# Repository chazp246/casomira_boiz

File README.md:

# Moje repo na desky atd. 
Nějaký to základní verzovaní
+ používat nějaký ten time tracker na hodiny
+ tabulka s BOM a náklady https://docs.google.com/spreadsheets/d/1U5YpFSBs-wufp3I8VY69B08vQyyNULmpqPkYMU48hfg/edit?usp=sharing

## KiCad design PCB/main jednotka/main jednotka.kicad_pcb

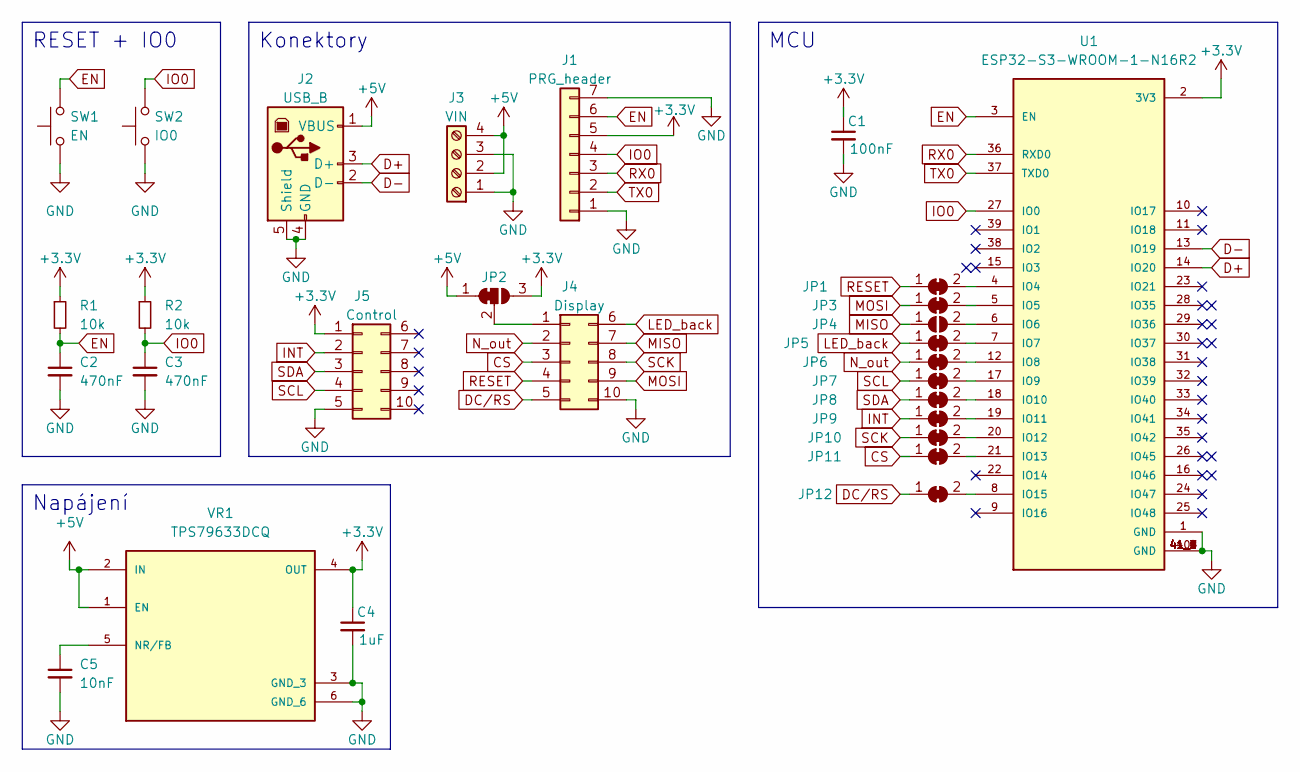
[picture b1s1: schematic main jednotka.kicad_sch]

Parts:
C1: 100nF; C_0805_2012Metric_Pad1.18x1.45mm_HandSolder
C2, C3: 470nF; C_0805_2012Metric
C4: 1uF; C_0805_2012Metric_Pad1.18x1.45mm_HandSolder
C5: 10nF; C_0805_2012Metric_Pad1.18x1.45mm_HandSolder
J1: PRG_header; PinHeader_1x07_P2.54mm_Vertical
J2: USB_B; PinHeader_1x04_P2.54mm_Vertical
J3: VIN; TerminalBlock_RND_205-00014_1x04_P5.00mm_Horizontal
J4: Display; PinSocket_2x05_P2.54mm_Vertical
J5: Control; PinSocket_2x05_P2.54mm_Vertical
JP1, JP3, JP5, JP6, JP7, JP8, JP9, JP10, JP11, JP12: SolderJumper_2_Bridged; SolderJumper-2_P1.3mm_Bridged_RoundedPad1.0x1.5mm
JP2: SolderJumper_3_Bridged12; SolderJumper-3_P1.3mm_Bridged12_RoundedPad1.0x1.5mm
JP4: jumper
R1, R2: 10k; R_0805_2012Metric
SW1: EN; SW_SPST_CK_RS282G05A3
SW2: IO0; SW_SPST_CK_RS282G05A3
U1: ESP32-S3-WROOM-1-N16R2; XCVR_ESP32-S3-WROOM-1-N16R2; PARTREV v1.0
VR1: TPS79633DCQ; VREG_TPS79633DCQ; PARTREV P

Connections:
+3.3V: C1.1, C4.1, J1.5, J5.1, JP2.3 (B), R1.1, R2.1, U1.2 (3V3), VR1.4 (OUT)
+5V: J2.1 (VBUS), J3.2, J3.4, JP2.1 (A), VR1.1 (EN), VR1.2 (IN)
CS: J4.3, JP11.1 (A)
D+: J2.3 (D+), U1.14 (IO20)
D-: J2.2 (D-), U1.13 (IO19)
DC/RS: J4.5, JP12.1 (A)
EN: C2.1, J1.6, R1.2, SW1.2, U1.3 (EN); also elsewhere on the board
GND: C1.2, C2.2, C3.2, C4.2, C5.2, J1.1, J1.7, J2.4 (GND), J2.5 (Shield), J3.1, J3.3, J4.10, J5.5, SW1.1, SW2.1, U1.1 (GND), U1.40 (GND), U1.41_1 (GND), U1.41_2 (GND), U1.41_3 (GND), U1.41_4 (GND), U1.41_5 (GND), U1.41_6 (GND), U1.41_7 (GND), U1.41_8 (GND), U1.41_9 (GND), U1.41_10, U1.41_11, U1.41_12, U1.41_13, U1.41_14, U1.41_15, U1.41_16, U1.41_17, U1.41_18, U1.41_19, U1.41_20, U1.41_21, VR1.3 (GND_3), VR1.6 (GND_6), VR1.7, VR1.8, VR1.9, VR1.10, VR1.11, VR1.12, VR1.13, VR1.14, VR1.15, VR1.16; also elsewhere on the board
INT: J5.2, JP9.1 (A)
IO0: C3.1, J1.4, R2.2, SW2.2, U1.27 (IO0); also elsewhere on the board
LED_back: J4.6, JP5.1 (A)
MISO: J4.7, JP4.1 (A)
MOSI: J4.9, JP3.1 (A)
N_out: J4.2, JP6.1 (A)
unnamed: C5.1, VR1.5 (NR/FB)
unnamed: J4.1, JP2.2 (C)
unnamed: JP1.2 (B), U1.4 (IO4)
unnamed: JP3.2 (B), U1.5 (IO5)
unnamed: JP4.2 (B), U1.6 (IO6)
unnamed: JP5.2 (B), U1.7 (IO7)
unnamed: JP12.2 (B), U1.8 (IO15)
unnamed: JP6.2 (B), U1.12 (IO8)
unnamed: JP7.2 (B), U1.17 (IO9)
unnamed: JP8.2 (B), U1.18 (IO10)
unnamed: JP9.2 (B), U1.19 (IO11)
unnamed: JP10.2 (B), U1.20 (IO12)
unnamed: JP11.2 (B), U1.21 (IO13)
RESET: J4.4, JP1.1 (A)
RX0: J1.3, U1.36 (RXD0)
SCK: J4.8, JP10.1 (A)
SCL: J5.4, JP7.1 (A)
SDA: J5.3, JP8.1 (A)
TX0: J1.2, U1.37 (TXD0)

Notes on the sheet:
Napájení
RESET + IO0
MCU
Konektory

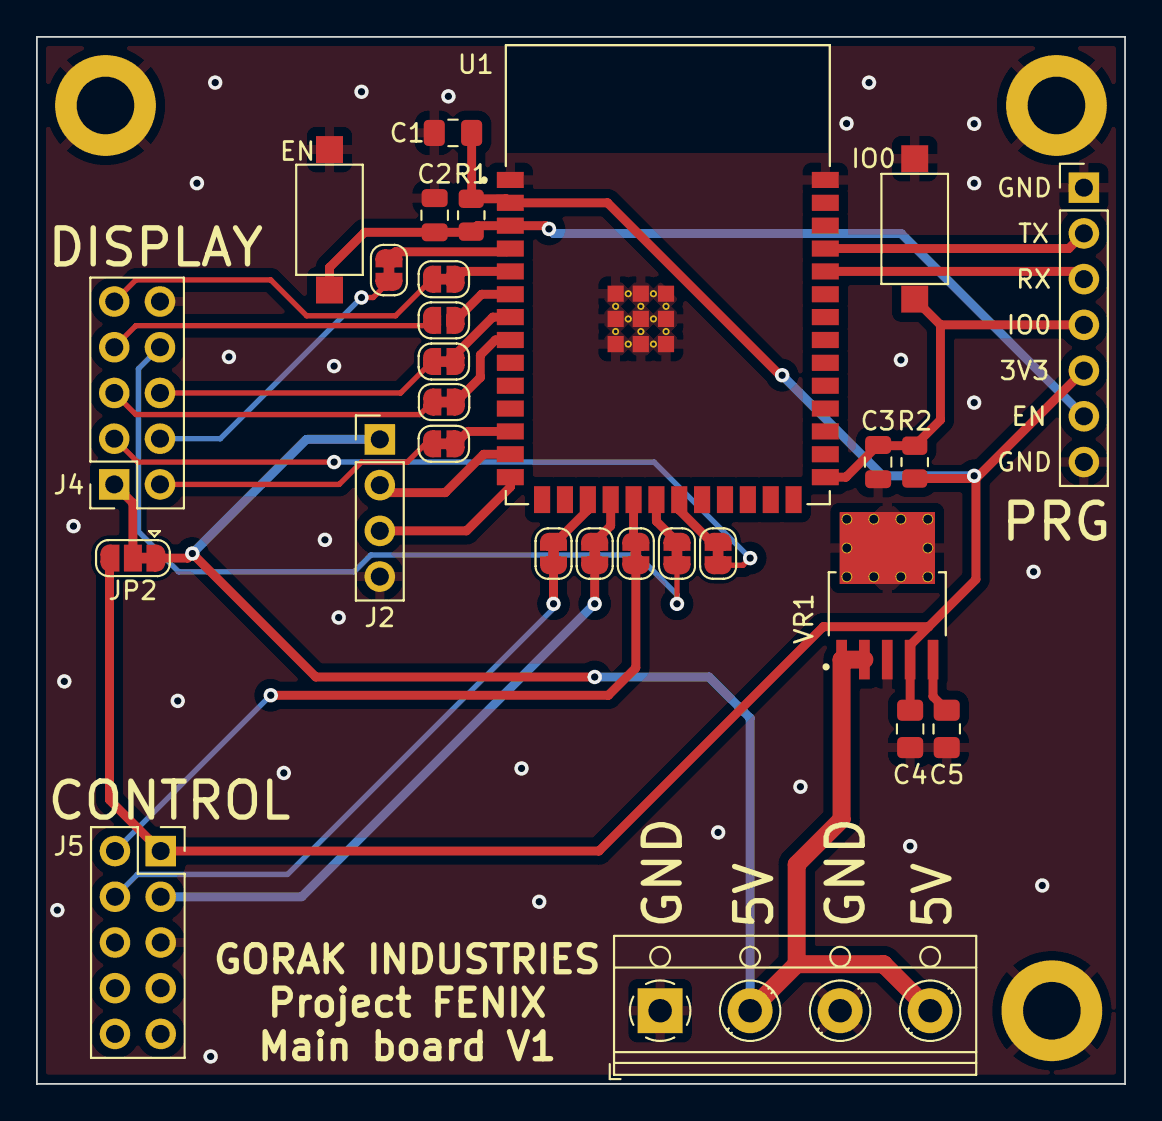
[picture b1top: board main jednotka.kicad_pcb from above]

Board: 2 copper layers, 60.5 x 58.2 mm, 28 parts (0 on the bottom side), 33 nets.

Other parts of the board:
EN: EN; SW_SPST_CK_RS282G05A3
IO0: IO0; SW_SPST_CK_RS282G05A3

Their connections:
EN: EN.2; also elsewhere on the board
GND: EN.1, IO0.1; also elsewhere on the board
IO0: IO0.2; also elsewhere on the board

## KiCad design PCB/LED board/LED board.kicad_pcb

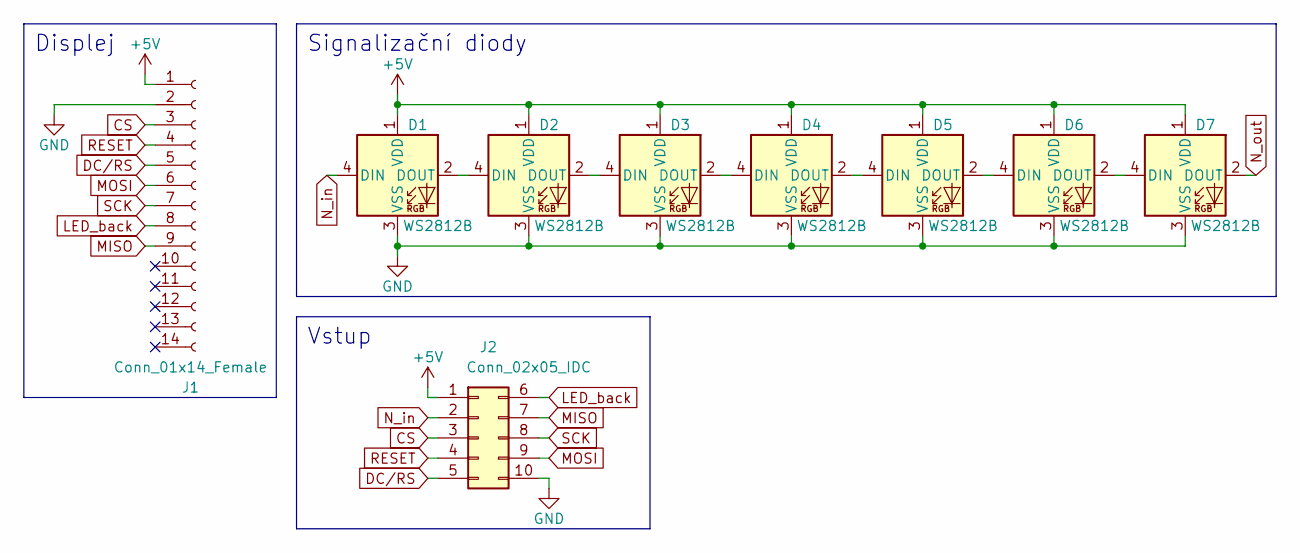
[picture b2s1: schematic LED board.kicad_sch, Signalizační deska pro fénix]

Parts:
D1, D2, D3, D4, D5, D6, D7: WS2812B; LED_WS2812B_PLCC4_5.0x5.0mm_P3.2mm
J1: Conn_01x14_Female; PinHeader_1x14_P2.54mm_Vertical
J2: Conn_02x05_IDC; PinSocket_2x05_P2.54mm_Horizontal

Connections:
+5V: D1.1 (VDD), D2.1 (VDD), D3.1 (VDD), D4.1 (VDD), D5.1 (VDD), D6.1 (VDD), D7.1 (VDD), J1.1, J2.1
CS: J1.3, J2.3
DC/RS: J1.5, J2.5
GND: D1.3 (VSS), D2.3 (VSS), D3.3 (VSS), D4.3 (VSS), D5.3 (VSS), D6.3 (VSS), D7.3 (VSS), J1.2, J2.10
LED_back: J1.8, J2.6
MISO: J1.9, J2.7
MOSI: J1.6, J2.9
N_in: D1.4 (DIN), J2.2
N_out: D7.2 (DOUT)
unnamed: D1.2 (DOUT), D2.4 (DIN)
unnamed: D2.2 (DOUT), D3.4 (DIN)
unnamed: D3.2 (DOUT), D4.4 (DIN)
unnamed: D4.2 (DOUT), D5.4 (DIN)
unnamed: D5.2 (DOUT), D6.4 (DIN)
unnamed: D6.2 (DOUT), D7.4 (DIN)
RESET: J1.4, J2.4
SCK: J1.7, J2.8

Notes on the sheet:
Vstup
Signalizační diody
Displej

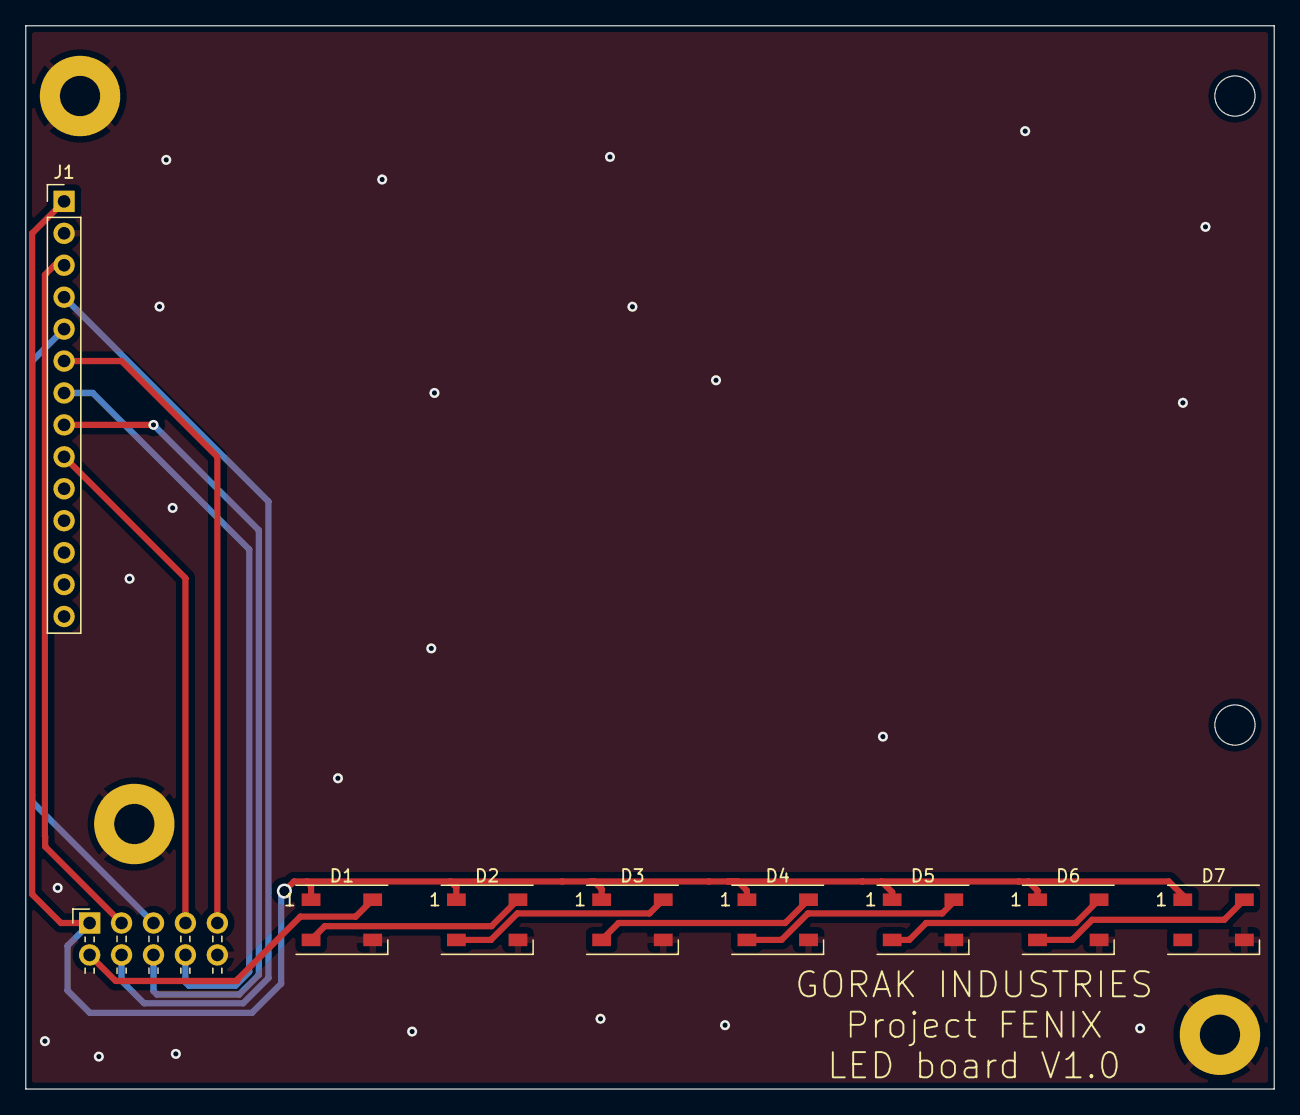
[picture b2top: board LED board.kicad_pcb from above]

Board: 2 copper layers, 99.3 x 84.6 mm, 9 parts (0 on the bottom side), 16 nets.

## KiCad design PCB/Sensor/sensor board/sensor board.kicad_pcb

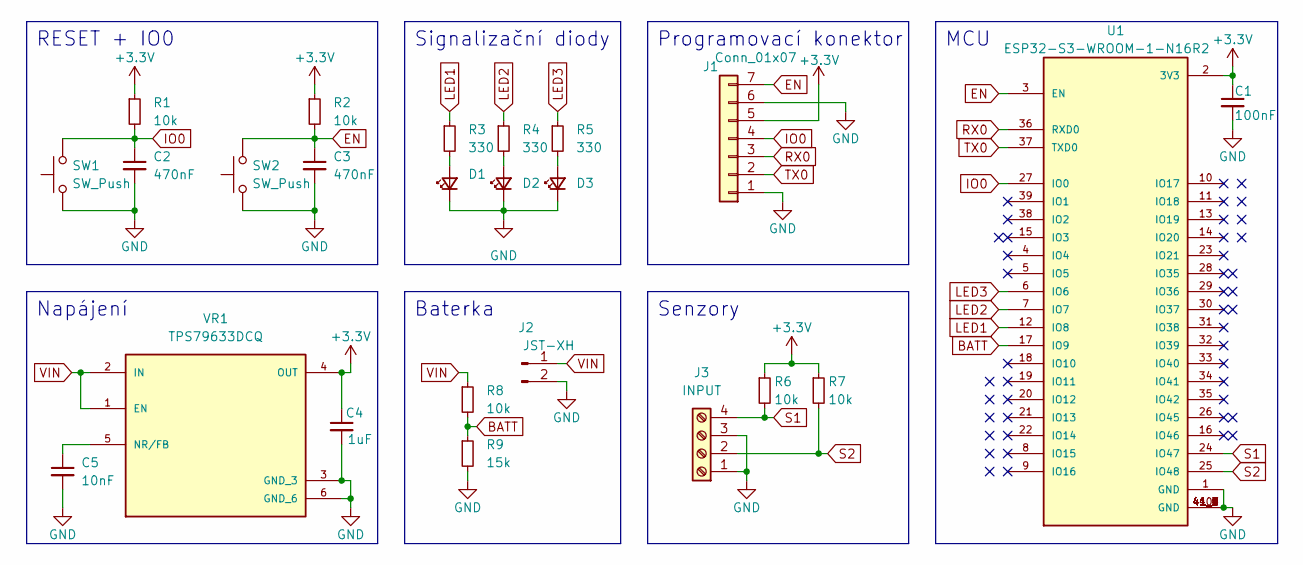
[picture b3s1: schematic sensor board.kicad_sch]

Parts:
C1: 100nF; C_0805_2012Metric_Pad1.18x1.45mm_HandSolder
C2, C3: 470nF; C_0805_2012Metric_Pad1.18x1.45mm_HandSolder
C4: 1uF; C_0805_2012Metric_Pad1.18x1.45mm_HandSolder
C5: 10nF; C_0805_2012Metric_Pad1.18x1.45mm_HandSolder
D1, D2, D3: LED_Small; LED_0805_2012Metric_Pad1.15x1.40mm_HandSolder
J1: Conn_01x07; PinHeader_1x07_P2.54mm_Vertical
J2: JST-XH; PinHeader_1x02_P2.54mm_Vertical
J3: INPUT; TerminalBlock_RND_205-00014_1x04_P5.00mm_Horizontal
R1, R2, R6, R7, R8: 10k; R_0805_2012Metric_Pad1.20x1.40mm_HandSolder
R3, R4, R5: 330; R_0805_2012Metric_Pad1.20x1.40mm_HandSolder
R9: 15k; R_0805_2012Metric_Pad1.20x1.40mm_HandSolder
SW1, SW2: SW_Push; SW_SPST_CK_RS282G05A3
U1: ESP32-S3-WROOM-1-N16R2; XCVR_ESP32-S3-WROOM-1-N16R2; PARTREV v1.0
VR1: TPS79633DCQ; VREG_TPS79633DCQ; PARTREV P

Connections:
+3.3V: C1.1, C4.1, J1.5, R1.1, R2.1, R6.1, R7.1, U1.2 (3V3), VR1.4 (OUT)
BATT: R8.2, R9.1, U1.17 (IO9)
EN: C3.1, J1.7, R2.2, SW2.2, U1.3 (EN)
GND: C1.2, C2.2, C3.2, C4.2, C5.2, D1.1 (K), D2.1 (K), D3.1 (K), J1.1, J1.6, J2.2, J3.1, J3.3, R9.2, SW1.1, SW2.1, U1.1 (GND), U1.40 (GND), U1.41_1 (GND), U1.41_2 (GND), U1.41_3 (GND), U1.41_4 (GND), U1.41_5 (GND), U1.41_6 (GND), U1.41_7 (GND), U1.41_8 (GND), U1.41_9 (GND), U1.41_10, U1.41_11, U1.41_12, U1.41_13, U1.41_14, U1.41_15, U1.41_16, U1.41_17, U1.41_18, U1.41_19, U1.41_20, U1.41_21, VR1.3 (GND_3), VR1.6 (GND_6), VR1.7, VR1.8, VR1.9, VR1.10, VR1.11, VR1.12, VR1.13, VR1.14, VR1.15, VR1.16
IO0: C2.1, J1.4, R1.2, SW1.2, U1.27 (IO0)
LED1: R3.1, U1.12 (IO8)
LED2: R4.1, U1.7 (IO7)
LED3: R5.1, U1.6 (IO6)
unnamed: C5.1, VR1.5 (NR/FB)
unnamed: D1.2 (A), R3.2
unnamed: D2.2 (A), R4.2
unnamed: D3.2 (A), R5.2
RX0: J1.3, U1.36 (RXD0)
S1: J3.4, R6.2, U1.24 (IO47)
S2: J3.2, R7.2, U1.25 (IO48)
TX0: J1.2, U1.37 (TXD0)
VIN: J2.1, R8.1, VR1.1 (EN), VR1.2 (IN)

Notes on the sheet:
Napájení
RESET + IO0
Programovací konektor
Baterka
MCU
Signalizační diody
Senzory

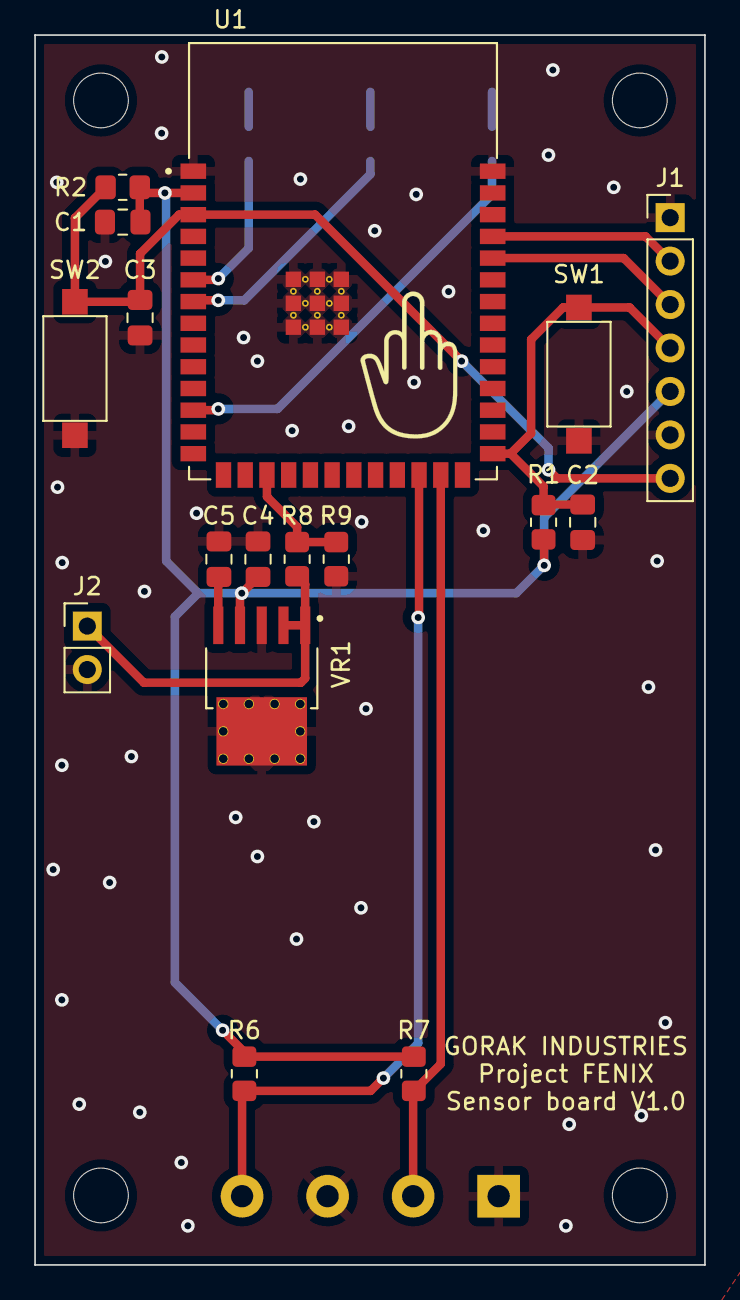
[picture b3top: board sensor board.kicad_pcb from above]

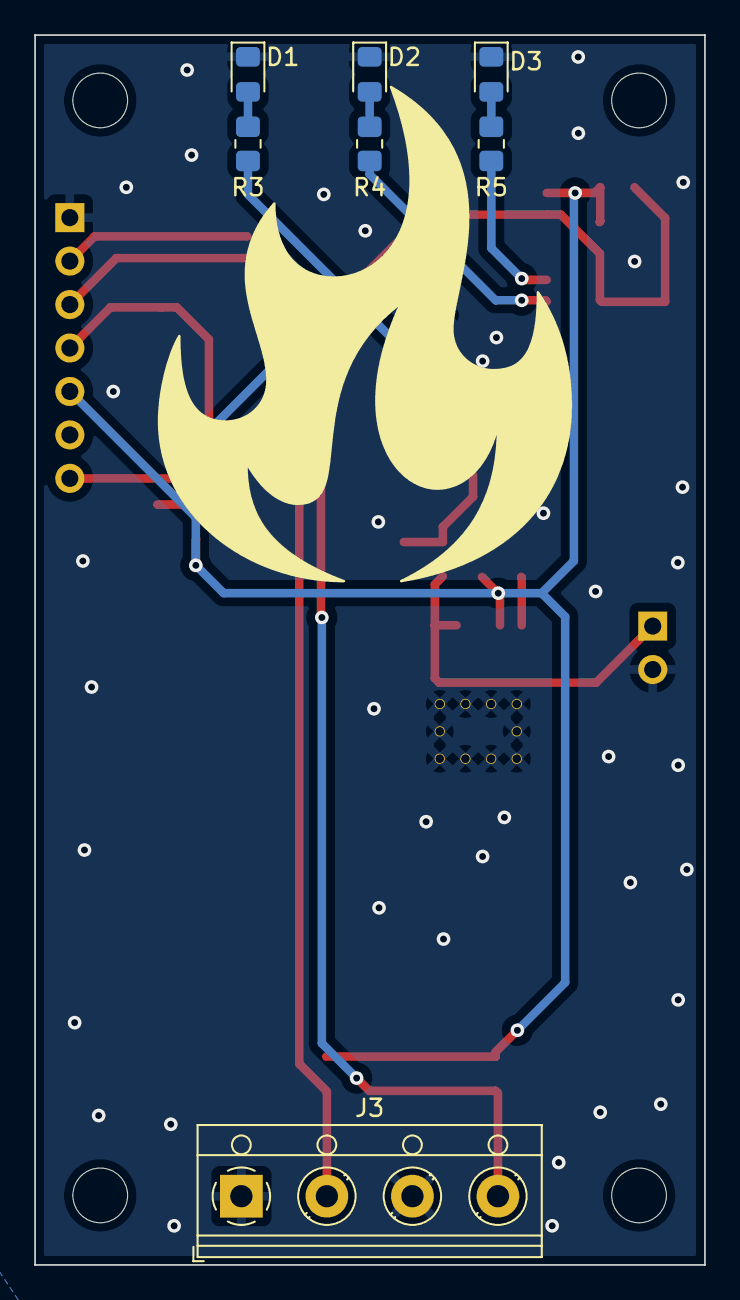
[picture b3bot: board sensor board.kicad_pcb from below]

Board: 2 copper layers, 39.2 x 71.9 mm, 24 parts (7 on the bottom side), 17 nets.

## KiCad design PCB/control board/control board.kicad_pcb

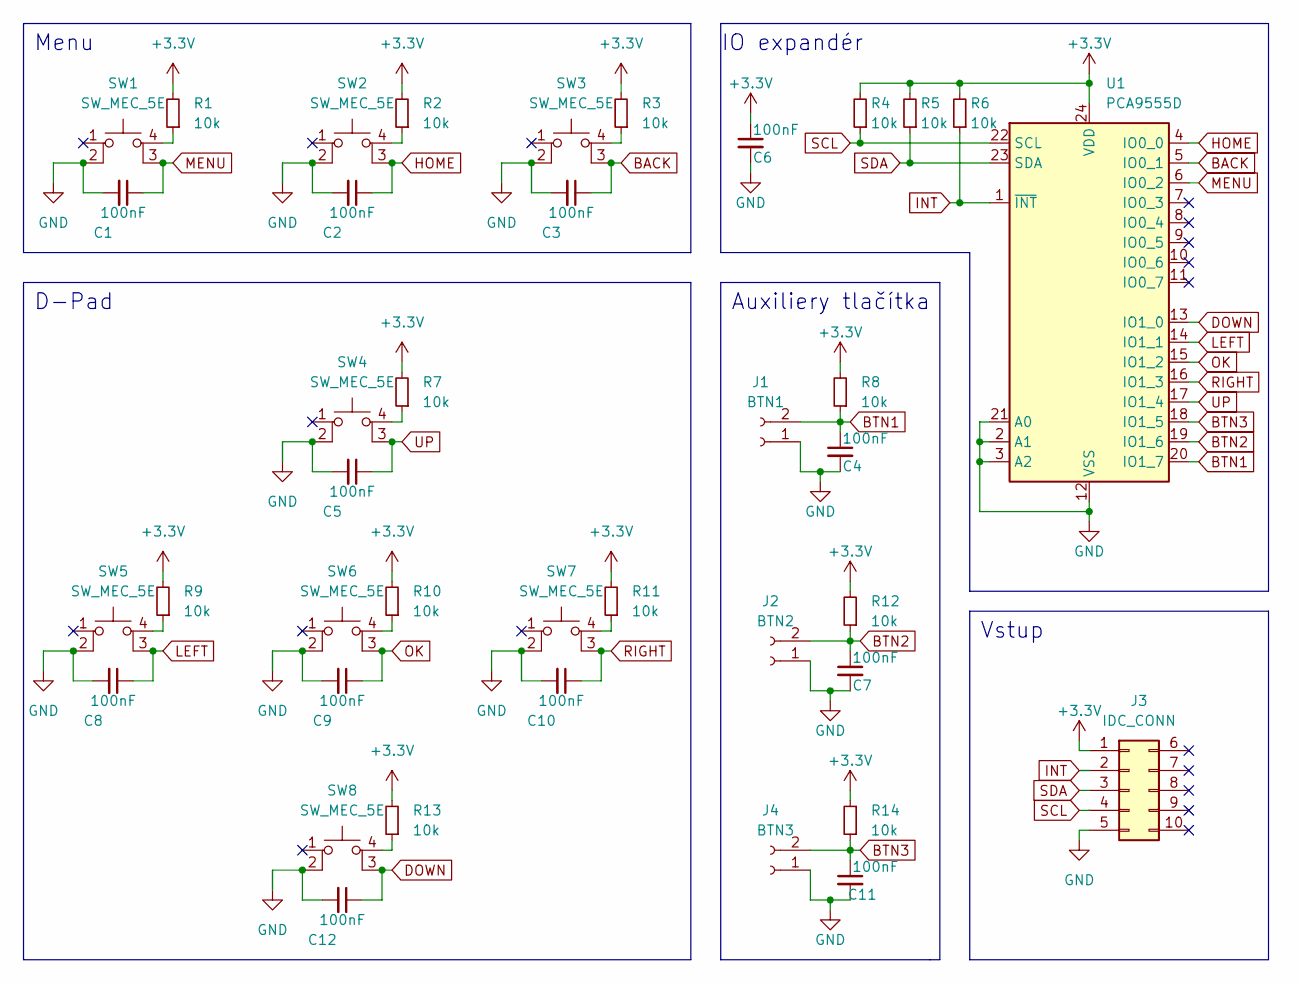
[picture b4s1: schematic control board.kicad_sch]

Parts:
C1, C2, C3, C4, C5, C6, C7, C8, C9, C10, C11, C12: 100nF; C_0805_2012Metric_Pad1.18x1.45mm_HandSolder
J1: BTN1; PinSocket_1x02_P2.54mm_Vertical
J2: BTN2; PinSocket_1x02_P2.54mm_Vertical
J3: IDC_CONN; PinSocket_2x05_P2.54mm_Vertical
J4: BTN3
R1, R2, R3, R4, R5, R6, R7, R8, R9, R10, R11, R12, R13, R14: 10k; R_0805_2012Metric_Pad1.20x1.40mm_HandSolder
SW1, SW2, SW3, SW4, SW5, SW6, SW7, SW8: SW_MEC_5E; TL3301SPF160QG
U1: PCA9555D; SOIC-24W_7.5x15.4mm_P1.27mm

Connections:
+3.3V: C6.1, J3.1, R1.2, R2.2, R3.2, R4.2, R5.2, R6.2, R7.2, R8.2, R9.2, R10.2, R11.2, R12.2, R13.2, R14.2, U1.24 (VDD)
BACK: C3.1, SW3.3 (K), U1.5 (IO0_1)
BTN1: C4.1, J1.2, R8.1, U1.20 (IO1_7)
BTN2: C7.1, J2.2, R12.1, U1.19 (IO1_6)
BTN3: C11.1, J4.2, R14.1, U1.18 (IO1_5)
DOWN: C12.1, SW8.3 (K), U1.13 (IO1_0)
GND: C1.2, C2.2, C3.2, C4.2, C5.2, C6.2, C7.2, C8.2, C9.2, C10.2, C11.2, C12.2, J1.1, J2.1, J3.5, J4.1, SW1.2, SW2.2, SW3.2, SW4.2, SW5.2, SW6.2, SW7.2, SW8.2, U1.2 (A1), U1.3 (A2), U1.12 (VSS), U1.21 (A0)
HOME: C2.1, SW2.3 (K), U1.4 (IO0_0)
INT: J3.2, R6.1, U1.1 (~INT)
LEFT: C8.1, SW5.3 (K), U1.14 (IO1_1)
MENU: C1.1, SW1.3 (K), U1.6 (IO0_2)
unnamed: R1.1, SW1.4 (A)
unnamed: R2.1, SW2.4 (A)
unnamed: R3.1, SW3.4 (A)
unnamed: R7.1, SW4.4 (A)
unnamed: R9.1, SW5.4 (A)
unnamed: R10.1, SW6.4 (A)
unnamed: R11.1, SW7.4 (A)
unnamed: R13.1, SW8.4 (A)
OK: C9.1, SW6.3 (K), U1.15 (IO1_2)
RIGHT: C10.1, SW7.3 (K), U1.16 (IO1_3)
SCL: J3.4, R4.1, U1.22 (SCL)
SDA: J3.3, R5.1, U1.23 (SDA)
UP: C5.1, SW4.3 (K), U1.17 (IO1_4)

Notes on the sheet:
Vstup
D-Pad
Menu
IO expandér
Auxiliery tlačítka

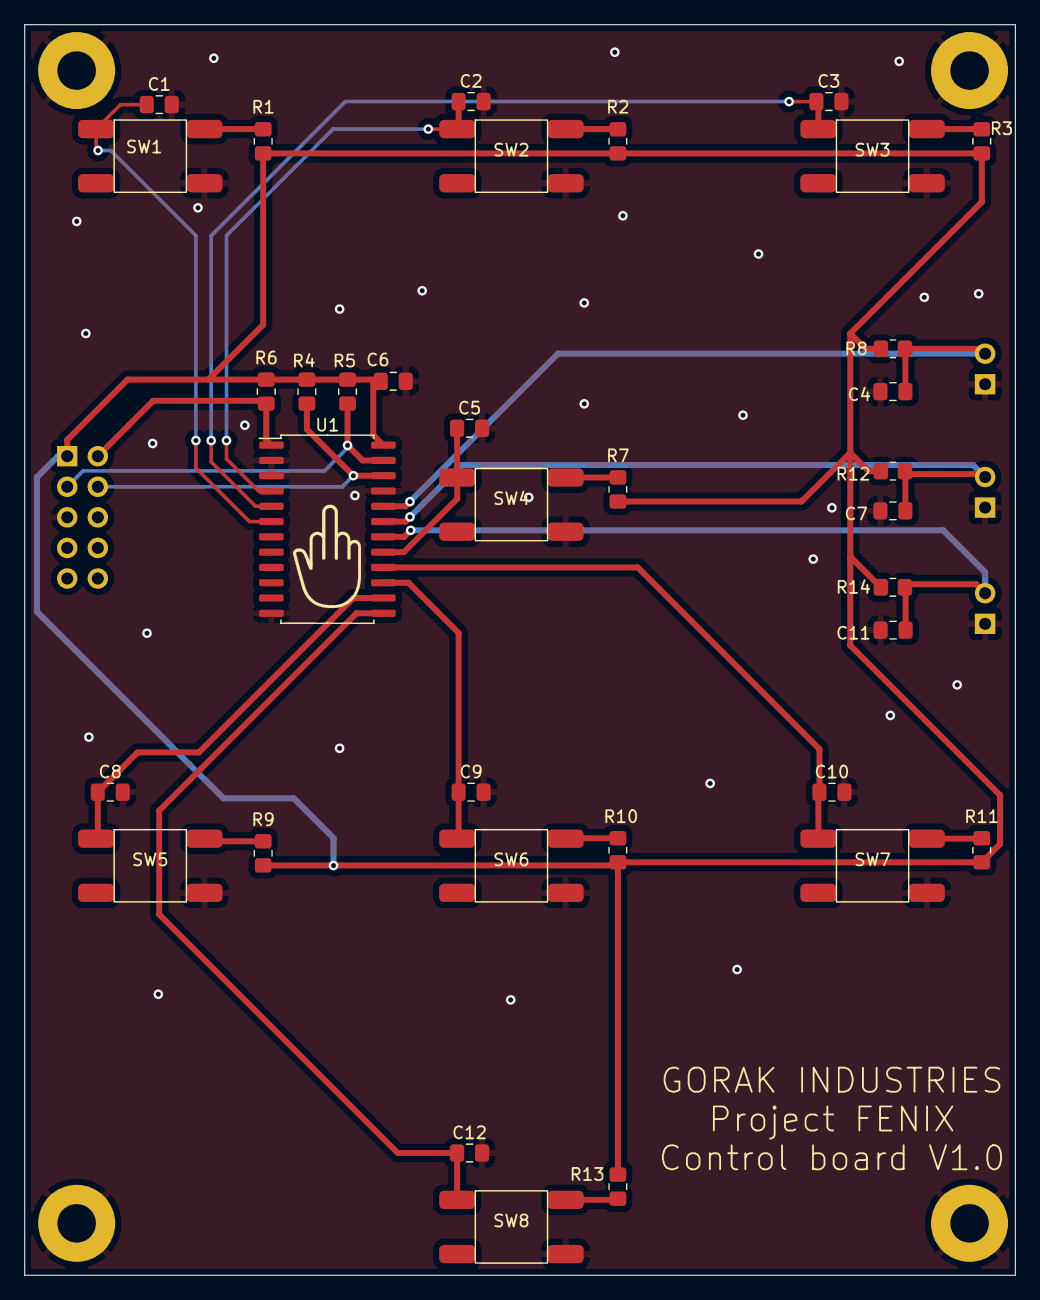
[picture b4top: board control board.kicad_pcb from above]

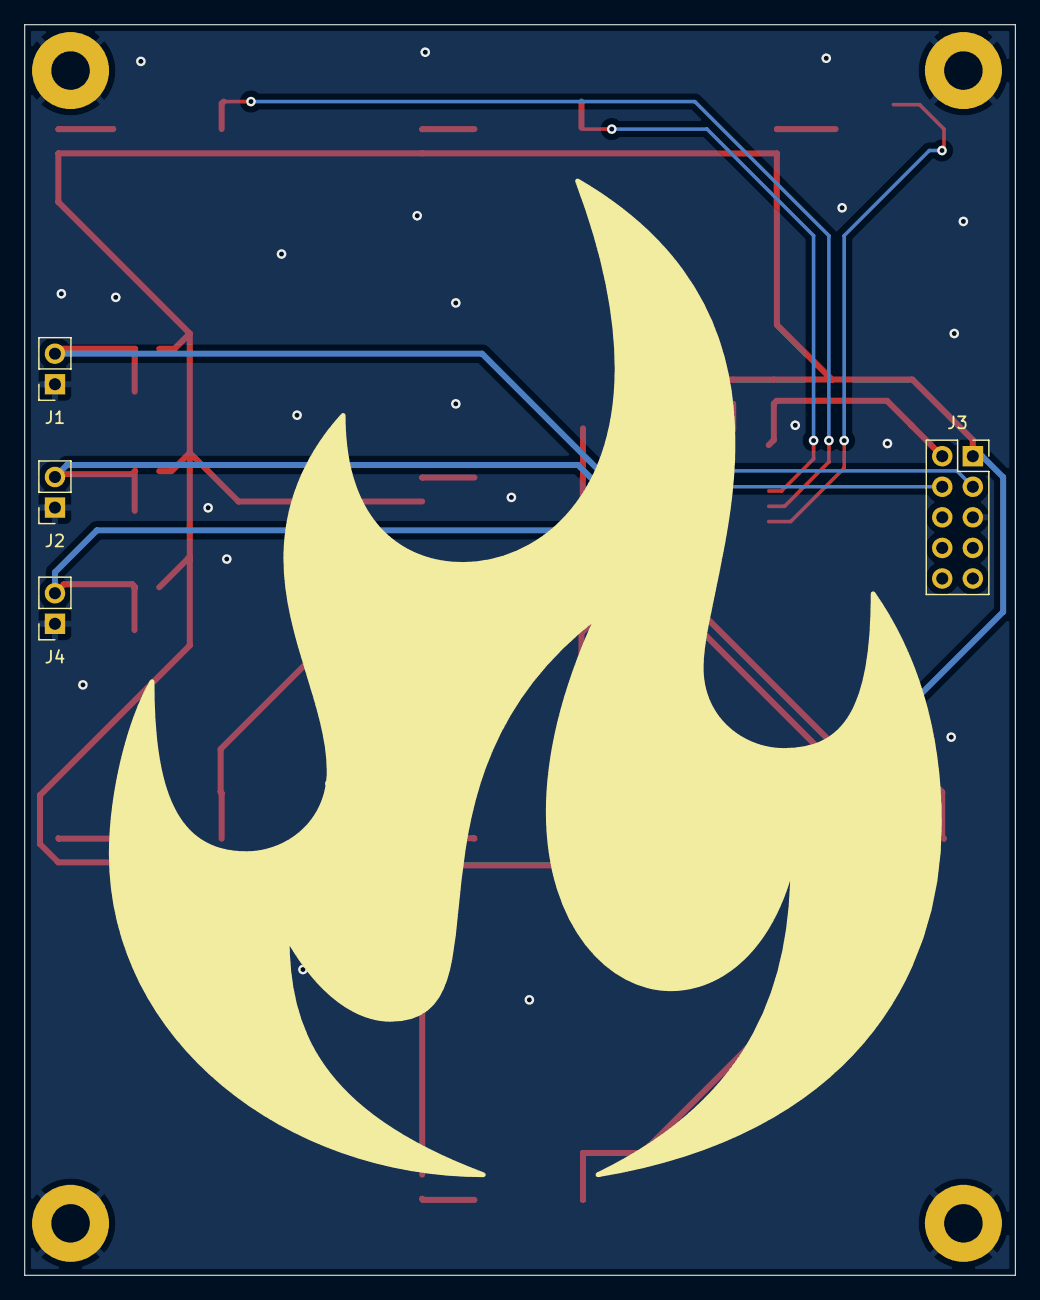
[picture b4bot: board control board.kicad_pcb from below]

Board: 2 copper layers, 82.3 x 103.9 mm, 39 parts (4 on the bottom side), 24 nets.

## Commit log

2023-02-26 esp32S3 base
2023-02-26 USB-C + ESP32 modely added
2023-04-12 Controll boarda schéma
2023-04-12 Control boarda a main board uprava
2023-04-12 footprint pro tlačítka a schéma pro control boardu
2023-04-14 Led board + control board
2023-04-15 control a led boarda hotový kromě popisku a děr
2023-04-15 mount pro control,LED board.Komplet sensor board
2023-04-15 Gerbery pro V1.0
2023-04-15 sensor V1.1 + gerbery
2023-05-10 Main jednotka V1 a objednavka jlcpcb
2023-05-19 vsechno hotovy kinda, desky osazeny a asi funkcni
2023-05-23 mockup
2023-05-23 f_paste u main jednotky test
2023-08-15 poslední verze desek
2023-08-15 uklizení souboru_V1.0
